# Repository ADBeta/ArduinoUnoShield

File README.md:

A simple, dual-sided protoboard shield for generic clone UNOs, while being compatible with official boards.

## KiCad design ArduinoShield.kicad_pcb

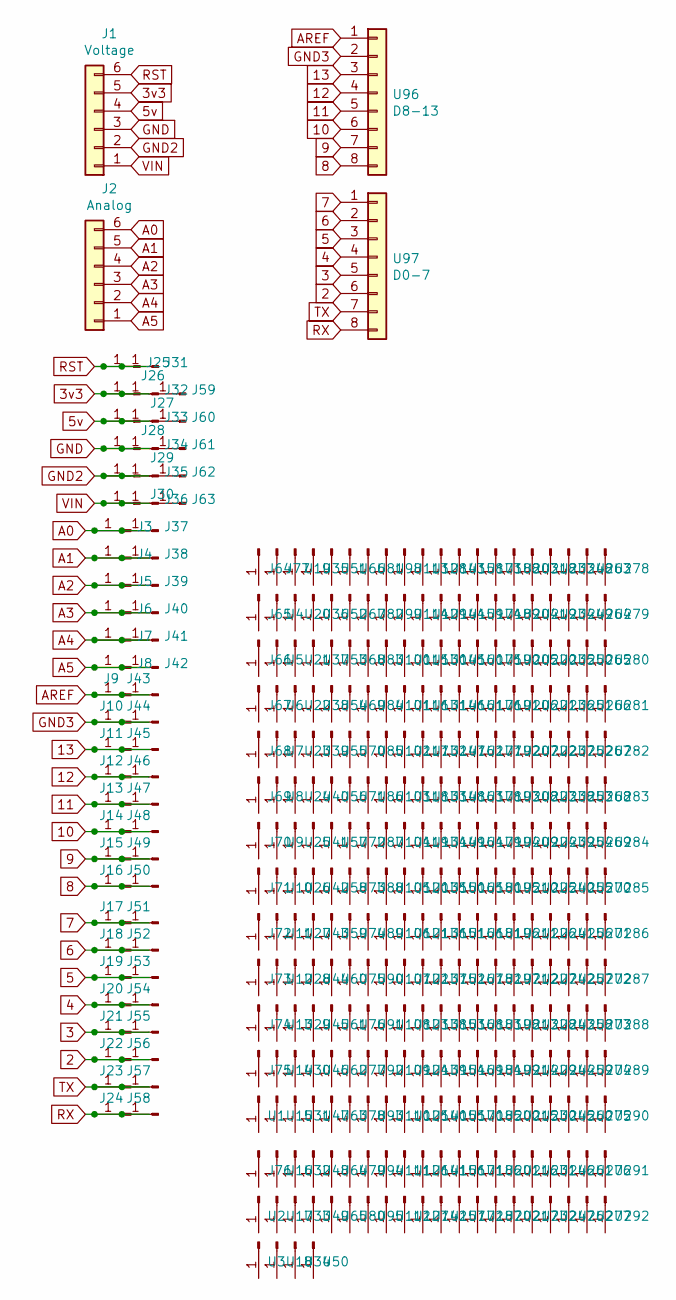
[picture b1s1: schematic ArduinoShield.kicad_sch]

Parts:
J1: Voltage; PinHeader_1x06_P2.54mm_Vertical
J2: Analog; PinHeader_1x06_P2.54mm_Vertical
J3, J4, J5, J6, J7, J8, J9, J10, J11, J12, J13, J14, J15, J16, J17, J18, J19, J20, J21, J22, J23, J24, J25, J26, J27, J28, J29, J30, J31, J32, J33, J34, J35, J36, J37, J38, J39, J40, J41, J42, J43, J44, J45, J46, J47, J48, J49, J50, J51, J52, J53, J54, J55, J56, J57, J58, J59, J60, J61, J62, J63, J64, J65, J66, J67, J68, J69, J70, J71, J72, J73, J74, J75, J76, J77: Hole; BasicHole
U1, U2, U3, U4, U5, U6, U7, U8, U9, U10, U11, U12, U13, U14, U15, U16, U17, U18, U19, U20, U21, U22, U23, U24, U25, U26, U27, U28, U29, U30, U31, U32, U33, U34, U35, U36, U37, U38, U39, U40, U41, U42, U43, U44, U45, U46, U47, U48, U49, U50, U51, U52, U53, U54, U55, U56, U57, U58, U59, U60, U61, U62, U63, U64, U65, U66, U67, U68, U69, U70, U71, U72, U73, U74, U75, U76, U77, U78, U79, U80, U81, U82, U83, U84, U85, U86, U87, U88, U89, U90, U91, U92, U93, U94, U95, U98, U99, U100, U101, U102, U103, U104, U105, U106, U107, U108, U109, U110, U111, U112, U113, U114, U115, U116, U117, U118, U119, U120, U121, U122, U123, U124, U125, U126, U127, U128, U129, U130, U131, U132, U133, U134, U135, U136, U137, U138, U139, U140, U141, U142, U143, U144, U145, U146, U147, U148, U149, U150, U151, U152, U153, U154, U155, U156, U157, U158, U159, U160, U161, U162, U163, U164, U165, U166, U167, U168, U169, U170, U171, U172, U173, U174, U175, U176, U177, U178, U179, U180, U181, U182, U183, U184, U185, U186, U187, U188, U189, U190, U191, U192, U193, U194, U195, U196, U197, U198, U199, U200, U201, U202, U203, U204, U205, U206, U207, U208, U209, U210, U211, U212, U213, U214, U215, U216, U217, U218, U219, U220, U221, U222, U223, U224, U225, U226, U227, U228, U229, U230, U231, U232, U233, U234, U235, U236, U237, U238, U239, U240, U241, U242, U243, U244, U245, U246, U247, U248, U249, U250, U251, U252, U253, U254, U255, U256, U257, U258, U259, U260, U261, U262, U263, U264, U265, U266, U267, U268, U269, U270, U271, U272, U273, U274, U275, U276, U277, U278, U279, U280, U281, U282, U283, U284, U285, U286, U287, U288, U289, U290, U291, U292: Hole; BasicHole
U96: D8-13; PinHeader_1x08_P2.54mm_Vertical
U97: D0-7; PinHeader_1x08_P2.54mm_Vertical

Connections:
2: J22.1, J56.1, U97.6
3: J21.1, J55.1, U97.5
3v3: J1.5, J26.1, J32.1, J59.1
4: J20.1, J54.1, U97.4
5: J19.1, J53.1, U97.3
5v: J1.4, J27.1, J33.1, J60.1
6: J18.1, J52.1, U97.2
7: J17.1, J51.1, U97.1
8: J16.1, J50.1, U96.8
9: J15.1, J49.1, U96.7
10: J14.1, J48.1, U96.6
11: J13.1, J47.1, U96.5
12: J12.1, J46.1, U96.4
13: J11.1, J45.1, U96.3
A0: J2.6, J3.1, J37.1
A1: J2.5, J4.1, J38.1
A2: J2.4, J5.1, J39.1
A3: J2.3, J6.1, J40.1
A4: J2.2, J7.1, J41.1
A5: J2.1, J8.1, J42.1
AREF: J9.1, J43.1, U96.1
GND: J1.3, J28.1, J34.1, J61.1
GND2: J1.2, J29.1, J35.1, J62.1
GND3: J10.1, J44.1, U96.2
RST: J1.6, J25.1, J31.1
RX: J24.1, J58.1, U97.8
TX: J23.1, J57.1, U97.7
VIN: J1.1, J30.1, J36.1, J63.1

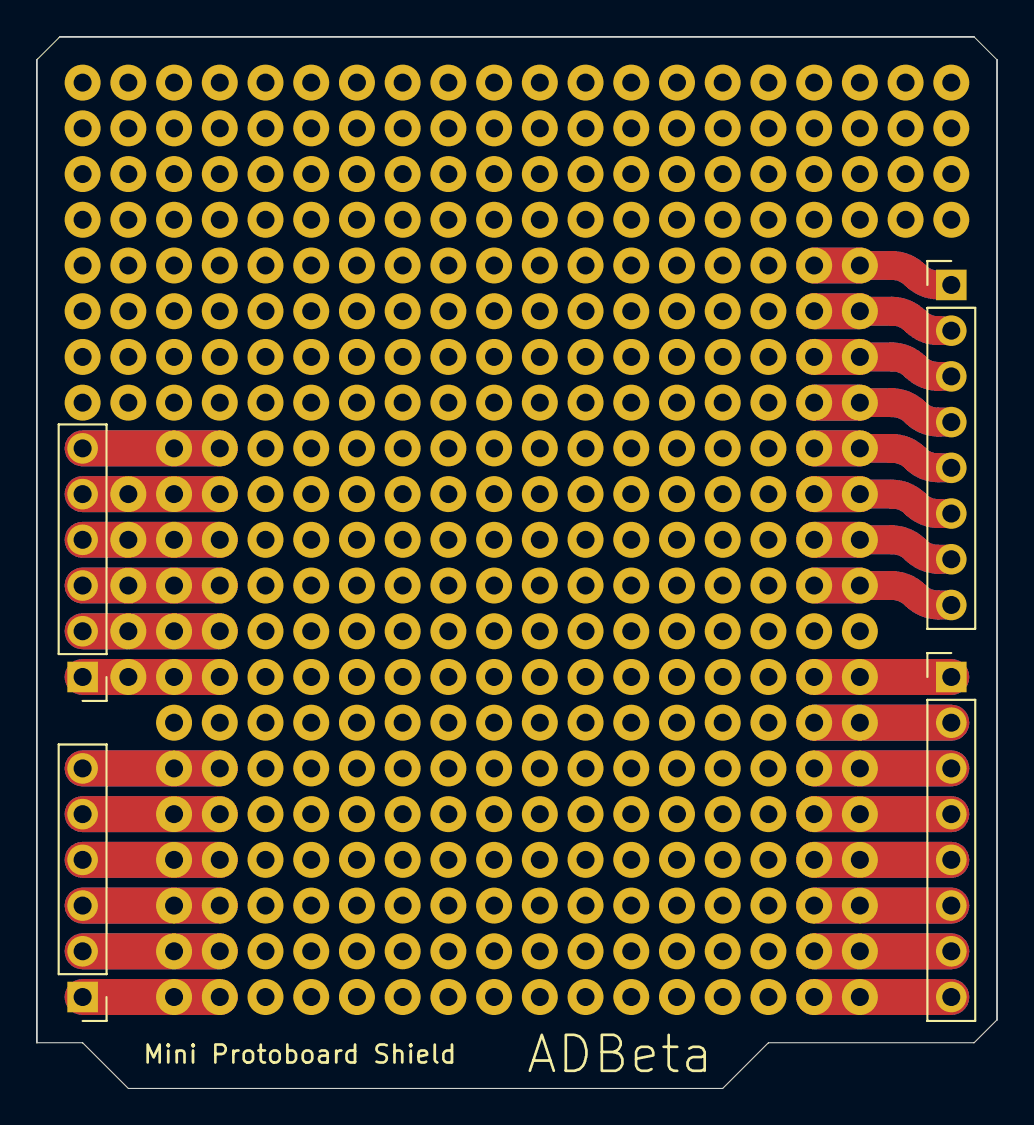
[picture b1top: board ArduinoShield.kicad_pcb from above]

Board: 2 copper layers, 53.3 x 58.4 mm, 369 parts (0 on the bottom side), 28 nets.

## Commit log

2022-10-31 Version 2
